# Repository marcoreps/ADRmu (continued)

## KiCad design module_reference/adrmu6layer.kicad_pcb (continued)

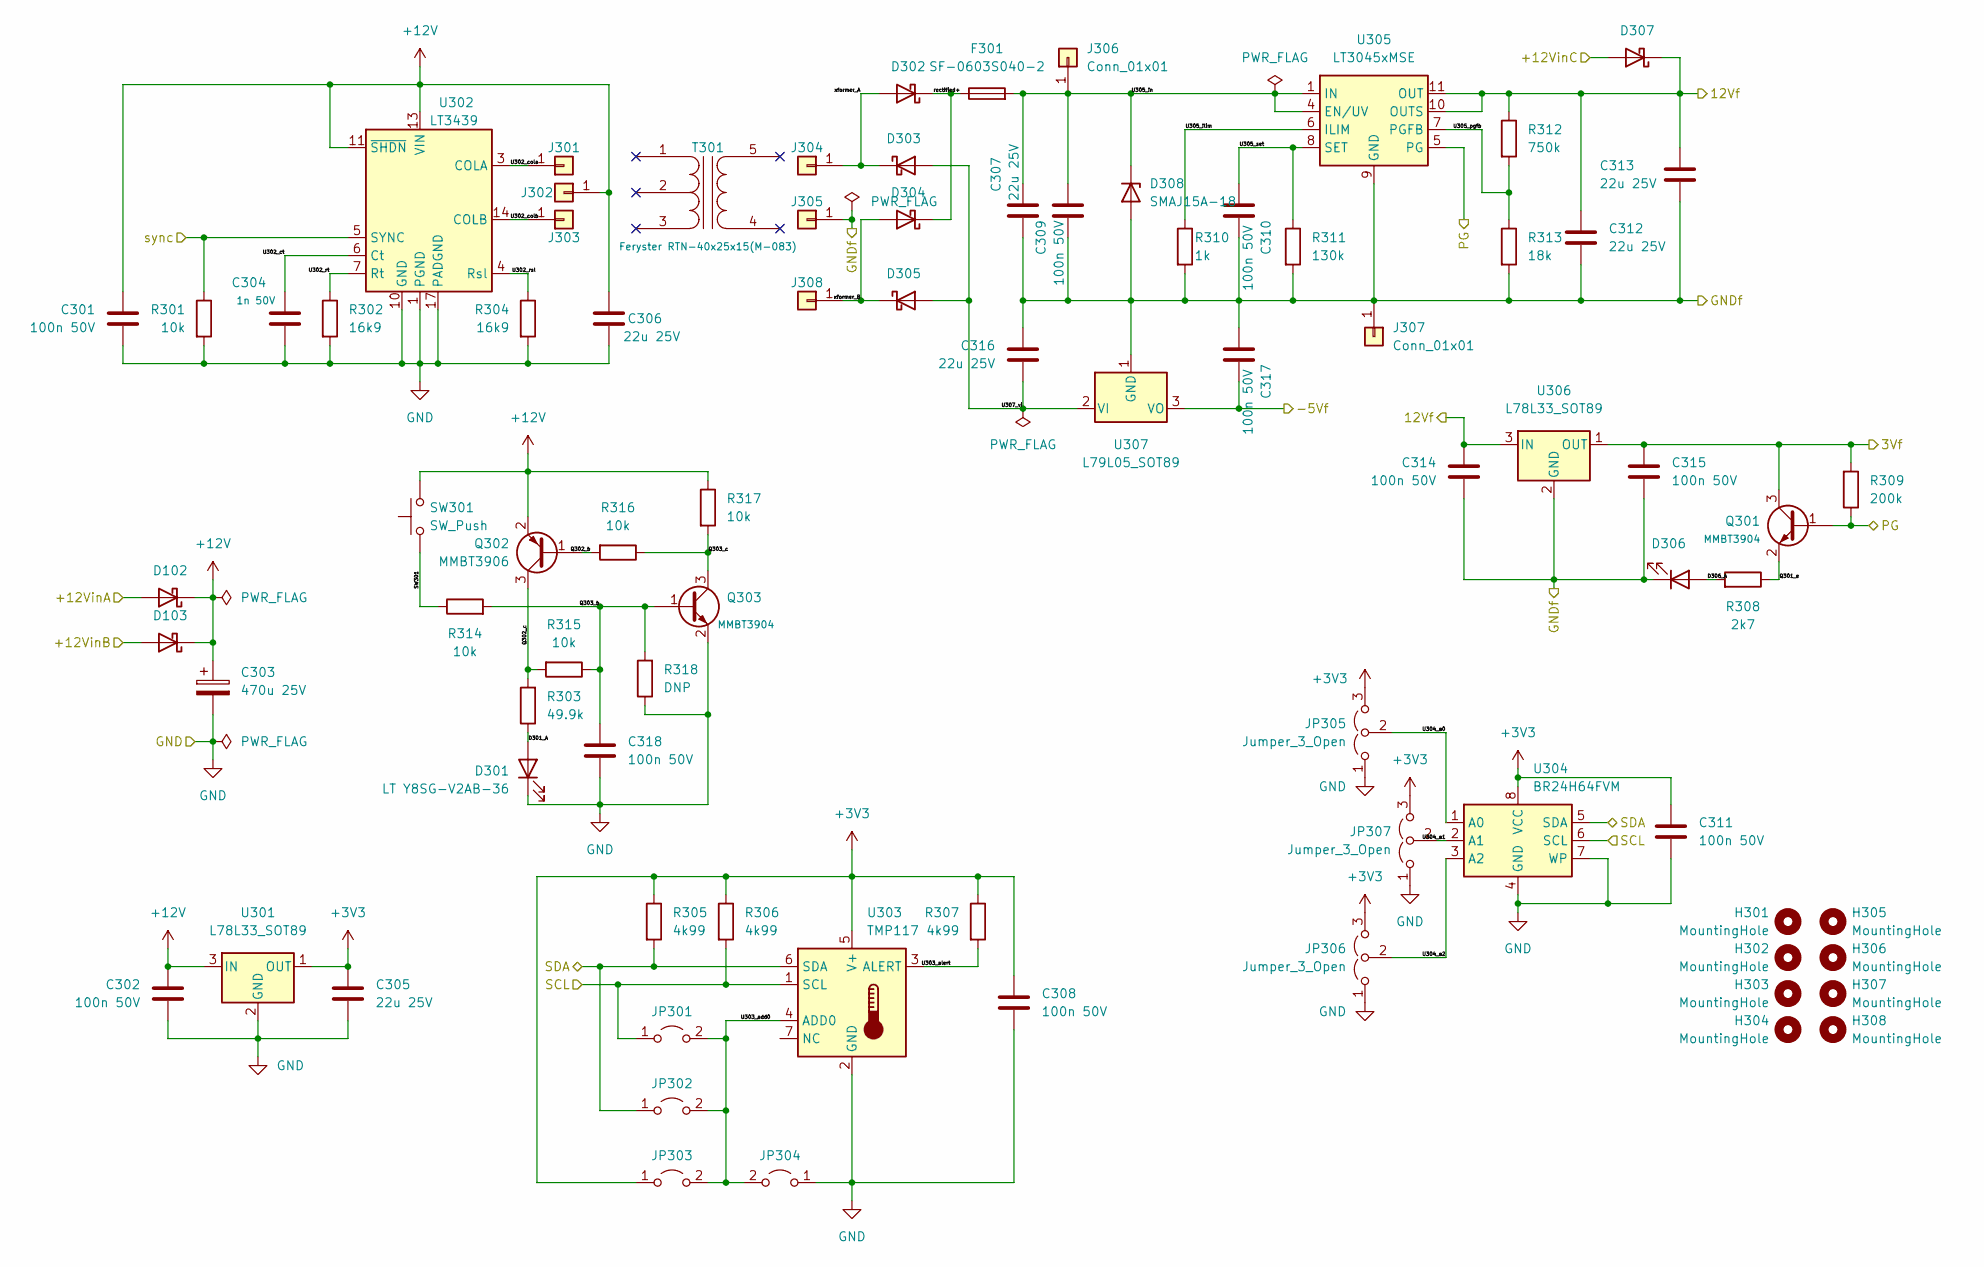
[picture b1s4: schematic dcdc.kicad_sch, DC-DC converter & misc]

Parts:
C301, C302, C308, C309, C310, C311, C314, C315, C317, C318: 100n 50V; C_0603_1608Metric
C303: 470u 25V; CP_Radial_D16.0mm_P7.50mm
C304: 1n 50V; C_0805_2012Metric
C305, C306, C307, C312, C313, C316: 22u 25V; C_1206_3216Metric
D102, D103, D302, D303, D304, D305, D307: PMEG6010CEH; D_SOD-123F
D301, D306: LT Y8SG-V2AB-36; LED_1206_3216Metric
D308: SMAJ15A-18; D_SMA
F301: SF-0603S040-2; Fuse_0603_1608Metric
H301, H302, H303, H304, H305, H306, H307, H308: MountingHole; MountingHole_4.3mm_M4
J301, J302, J303, J304, J305, J308: Conn_01x01; SolderWire-1sqmm_1x01_D1.4mm_OD3.9mm
J306, J307: Conn_01x01; SolderWirePad_1x01_SMD_1x2mm
JP301, JP302, JP303, JP304: Jumper_2_Open; SolderJumper-2_P1.3mm_Open_RoundedPad1.0x1.5mm
JP305, JP306, JP307: Jumper_3_Open; SolderJumper-3_P1.3mm_Open_RoundedPad1.0x1.5mm_NumberLabels
Q301, Q303: MMBT3904; SOT-23
Q302: MMBT3906; SOT-23
R301, R314, R315, R316, R317: 10k; R_0805_2012Metric
R302, R304: 16k9; R_0805_2012Metric
R303: 49.9k; R_0805_2012Metric
R305, R306, R307: 4k99; R_0805_2012Metric
R308: 2k7; R_0805_2012Metric
R309: 200k; R_0805_2012Metric
R310: 1k; R_0805_2012Metric
R311: 130k; R_0805_2012Metric
R312: 750k; R_0805_2012Metric
R313: 18k; R_0805_2012Metric
R318: DNP; R_0805_2012Metric
SW301: SW_Push; SW_Tactile_SPST_Angled_PTS645Vx31-2LFS
T301: Feryster RTN-40x25x15(M-083)
U301, U306: L78L33_SOT89; SOT-89-3
U302: LT3439; TSSOP-16-1EP_4.4x5mm_P0.65mm
U303: TMP117; WSON-6-1EP_2x2mm_P0.65mm_EP1x1.6mm
U304: BR24H64FVM; MSOP-8_3x3mm_P0.65mm
U305: LT3045xMSE; MSOP-12-1EP_3x4mm_P0.65mm_EP1.65x2.85mm
U307: L79L05_SOT89; SOT-89-3

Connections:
+3V3: C305.1, C308.1, C311.1, JP303.1 (A), JP305.3 (B), JP306.3 (B), JP307.3 (B), R305.1, R306.1, R307.1, U301.1 (OUT), U303.5 (V+), U304.8 (VCC)
+12V: C301.1, C302.1, C303.1, C306.1, D102.1 (K), D103.1 (K), J302.1, Q302.2 (E), R317.1, SW301.2, U301.3 (IN), U302.11 (~SHDN), U302.13 (VIN)
/Buffer/3Vf: C315.1, Q301.3 (C), R309.2, U306.1 (OUT); also elsewhere on the board
/Buffer/12Vf: C312.1, C313.1, C314.1, D307.1 (K), R312.1, U305.10 (OUTS), U305.11 (OUT), U305.12 (OUT), U306.3 (IN); also elsewhere on the board
/Buffer/-5Vf: C317.2, U307.3 (VO); also elsewhere on the board
/Buffer/FF: Q301.1 (B), R309.1, U305.5 (PG); also elsewhere on the board
/Buffer/GNDf: C307.2, C309.2, C310.2, C312.2, C313.2, C314.2, C315.2, C316.1, C317.1, D306.1 (K), D308.2 (A), J305.1, J307.1, R310.2, R311.2, R313.2, U305.9 (GND), U305.13 (GND), U306.2 (GND), U307.1 (GND); also elsewhere on the board
/DC-DC converter/+12VinA: D102.2 (A); also elsewhere on the board
/DC-DC converter/+12VinB: D103.2 (A); also elsewhere on the board
/DC-DC converter/+12VinC: D307.2 (A); also elsewhere on the board
/DC-DC converter/D301_A: D301.2 (A), R303.1
/DC-DC converter/D306_A: D306.2 (A), R308.2
/DC-DC converter/Q301_e: Q301.2 (E), R308.1
/DC-DC converter/Q302_b: Q302.1 (B), R316.2
/DC-DC converter/Q302_c: Q302.3 (C), R303.2, R315.2
/DC-DC converter/Q303_b: C318.1, Q303.1 (B), R314.2, R315.1, R318.2
/DC-DC converter/Q303_c: Q303.3 (C), R316.1, R317.2
/DC-DC converter/SCL: JP301.1 (A), R306.2, U303.1 (SCL), U304.6 (SCL); also elsewhere on the board
/DC-DC converter/SDA: JP302.1 (A), R305.2, U303.6 (SDA), U304.5 (SDA); also elsewhere on the board
/DC-DC converter/SW301: R314.1, SW301.1
/DC-DC converter/U302_cola: J301.1, U302.3 (COLA)
/DC-DC converter/U302_colb: J303.1, U302.14 (COLB)
/DC-DC converter/U302_ct: C304.1, U302.6 (Ct)
/DC-DC converter/U302_rsl: R304.1, U302.4 (Rsl)
/DC-DC converter/U302_rt: R302.1, U302.7 (Rt)
/DC-DC converter/U303_add0: JP301.2 (B), JP302.2 (B), JP303.2 (B), JP304.2 (B), U303.4 (ADD0)
/DC-DC converter/U303_alert: R307.2, U303.3 (ALERT)
/DC-DC converter/U304_a0: JP305.2 (C), U304.1 (A0)
/DC-DC converter/U304_a1: JP307.2 (C), U304.2 (A1)
/DC-DC converter/U304_a2: JP306.2 (C), U304.3 (A2)
/DC-DC converter/U305_ilim: R310.1, U305.6 (ILIM)
/DC-DC converter/U305_in: C307.1, C309.1, D308.1 (K), F301.2, J306.1, U305.1 (IN), U305.2 (IN), U305.3 (IN), U305.4 (EN/UV)
/DC-DC converter/U305_pgfb: R312.2, R313.1, U305.7 (PGFB)
/DC-DC converter/U305_set: C310.1, R311.1, U305.8 (SET)
/DC-DC converter/U307_vi: C316.2, D303.2 (A), D305.2 (A), U307.2 (VI)
/DC-DC converter/rectified+: D302.1 (K), D304.1 (K), F301.1
/DC-DC converter/sync: R301.1, U302.5 (SYNC); also elsewhere on the board
/DC-DC converter/xformer_A: D302.2 (A), D303.1 (K), J304.1
/DC-DC converter/xformer_B: D304.2 (A), D305.1 (K), J308.1
GND: C301.2, C302.2, C303.2, C304.2, C305.2, C306.2, C308.2, C311.2, C318.2, D301.1 (K), JP304.1 (A), JP305.1 (A), JP306.1 (A), JP307.1 (A), Q303.2 (E), R301.2, R302.2, R304.2, R318.1, U301.2 (GND), U302.1 (PGND), U302.10 (GND), U302.16 (PGND), U302.17 (PADGND), U303.2 (GND), U304.4 (GND), U304.7 (WP); also elsewhere on the board

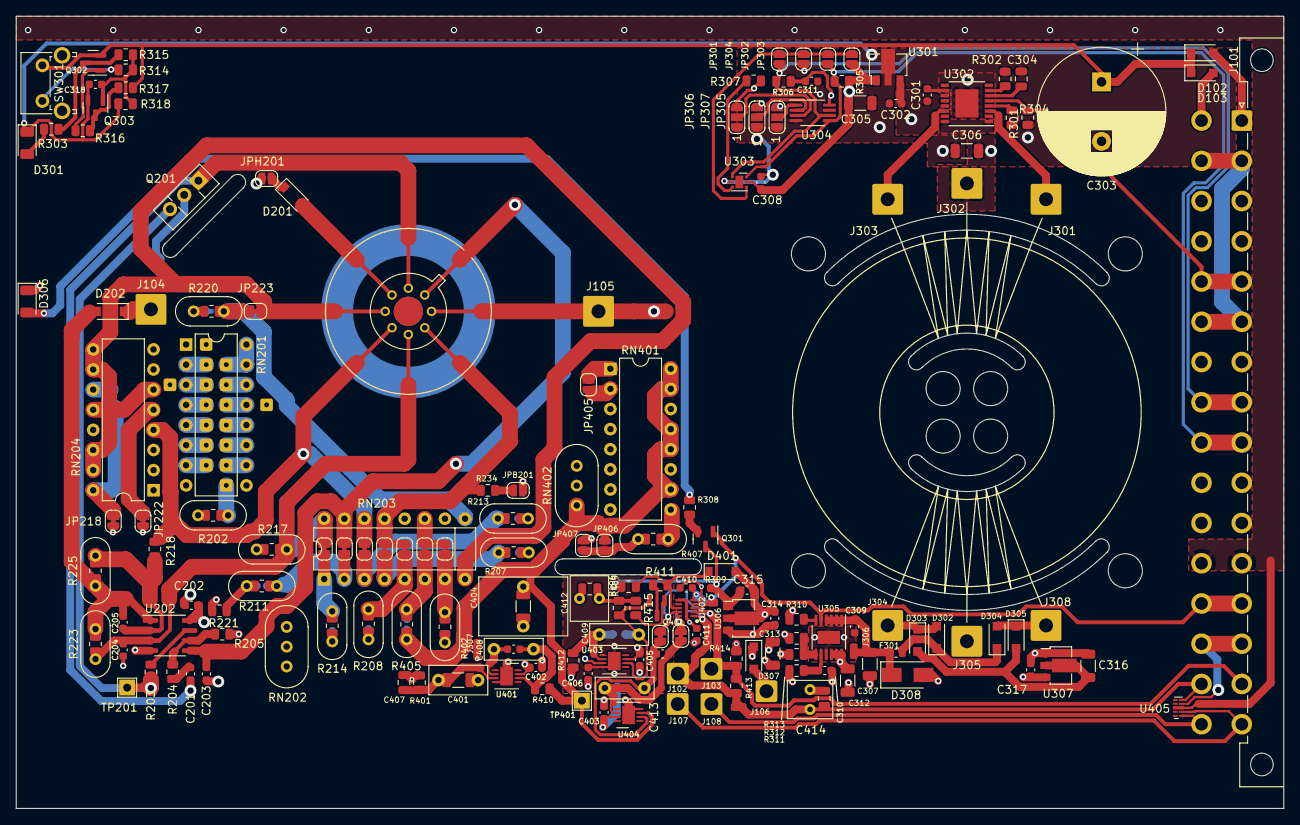
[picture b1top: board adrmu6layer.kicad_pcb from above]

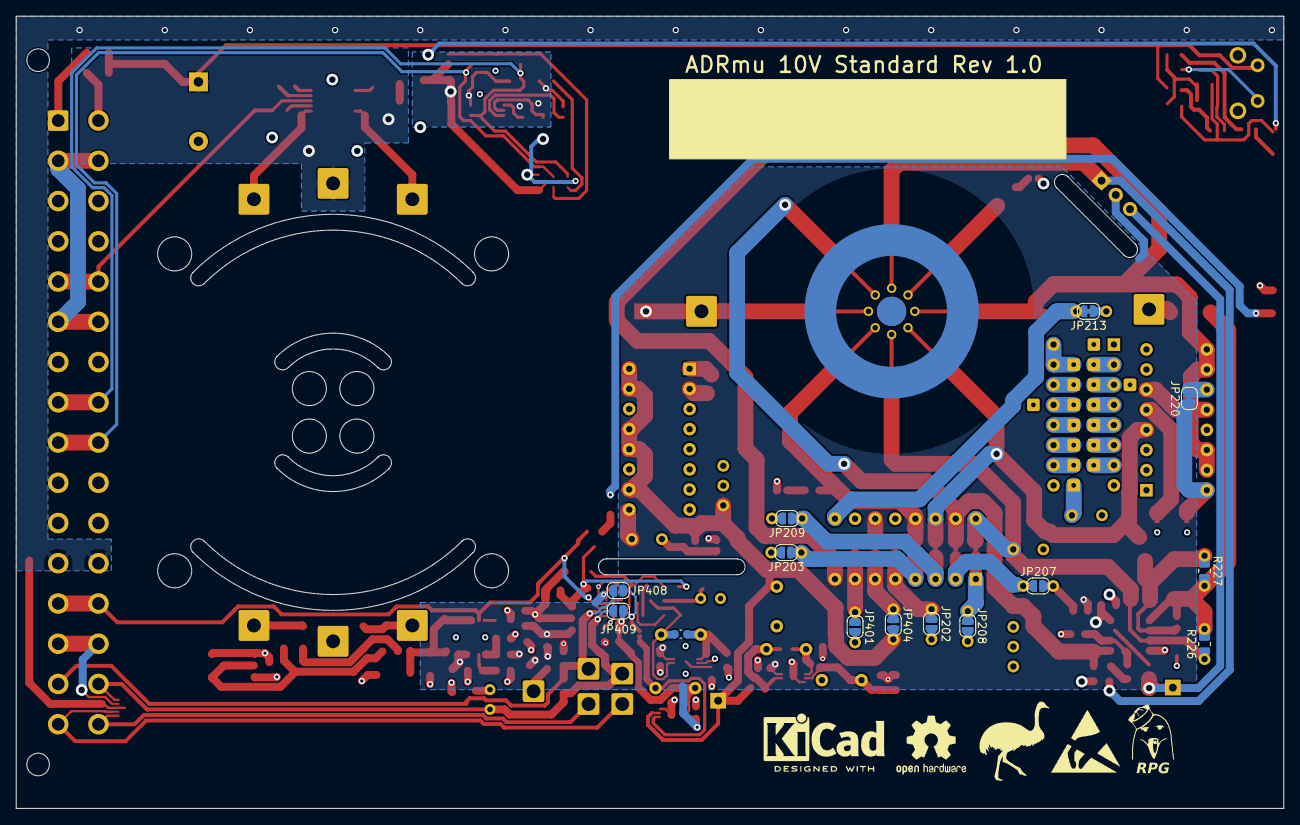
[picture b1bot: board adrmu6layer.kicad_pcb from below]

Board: 6 copper layers, 160.0 x 100.0 mm, 229 parts (19 on the bottom side), 101 nets.

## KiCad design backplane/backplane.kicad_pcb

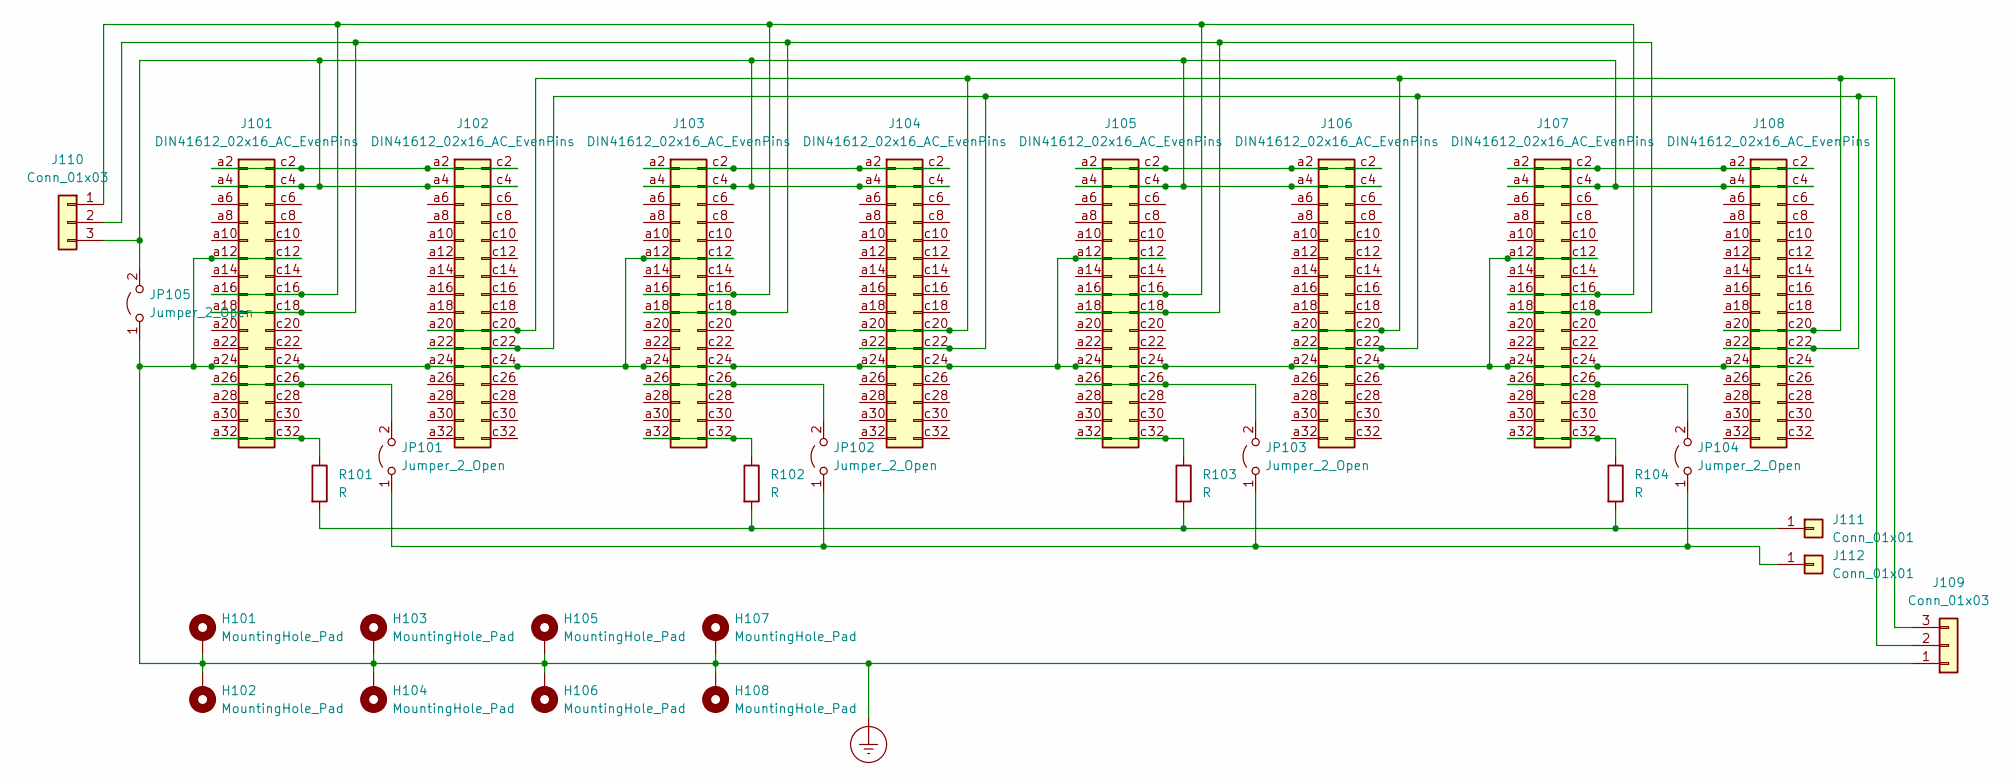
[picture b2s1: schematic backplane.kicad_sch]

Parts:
H101, H102, H103, H104, H105, H106, H107, H108: MountingHole_Pad; MountingHole_2.5mm_Pad
J101, J102, J103, J104, J105, J106, J107, J108: DIN41612_02x16_AC_EvenPins; DIN41612_C_2x16_Female_Vertical_THT
J109: Conn_01x03; TerminalBlock_WAGO_804-103_1x03_P5.00mm_45Degree
J110: Conn_01x03; JST_XH_B3B-XH-A_1x03_P2.50mm_Vertical
J111, J112: Conn_01x01; SolderWire-0.5sqmm_1x01_D0.9mm_OD2.1mm
JP101, JP102, JP103, JP104, JP105: Jumper_2_Open; SolderJumper-2_P1.3mm_Open_RoundedPad1.0x1.5mm
R101, R102, R103, R104: R; R_0805_2012Metric

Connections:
Earth_Protective: H101.1, H102.1, H103.1, H104.1, H105.1, H106.1, H107.1, H108.1, J101.a12, J101.a24, J101.c12, J101.c24, J102.a24, J102.c24, J103.a12, J103.a24, J103.c12, J103.c24, J104.a24, J104.c24, J105.a12, J105.a24, J105.c12, J105.c24, J106.a24, J106.c24, J107.a12, J107.a24, J107.c12, J107.c24, J108.a24, J108.c24, J109.1, JP105.1 (A)
unnamed: J101.a2, J101.c2, J102.a2, J102.c2
unnamed: J101.a16, J101.c16, J103.a16, J103.c16, J105.a16, J105.c16, J107.a16, J107.c16, J110.1
unnamed: J101.a18, J101.c18, J103.a18, J103.c18, J105.a18, J105.c18, J107.a18, J107.c18, J110.2
unnamed: J101.a26, J101.c26, JP101.2 (B)
unnamed: J101.a32, J101.c32, R101.1
unnamed: J102.a20, J102.c20, J104.a20, J104.c20, J106.a20, J106.c20, J108.a20, J108.c20, J109.3
unnamed: J102.a22, J102.c22, J104.a22, J104.c22, J106.a22, J106.c22, J108.a22, J108.c22, J109.2
unnamed: J103.a2, J103.c2, J104.a2, J104.c2
unnamed: J103.a26, J103.c26, JP102.2 (B)
unnamed: J103.a32, J103.c32, R102.1
unnamed: J105.a2, J105.c2, J106.a2, J106.c2
unnamed: J105.a26, J105.c26, JP103.2 (B)
unnamed: J105.a32, J105.c32, R103.1
unnamed: J107.a2, J107.c2, J108.a2, J108.c2
unnamed: J107.a26, J107.c26, JP104.2 (B)
unnamed: J107.a32, J107.c32, R104.1
unnamed: J101.a4, J101.c4, J102.a4, J102.c4, J103.a4, J103.c4, J104.a4, J104.c4, J105.a4, J105.c4, J106.a4, J106.c4, J107.a4, J107.c4, J108.a4, J108.c4, J110.3, JP105.2 (B)
unnamed: J111.1, R101.2, R102.2, R103.2, R104.2
unnamed: J112.1, JP101.1 (A), JP102.1 (A), JP103.1 (A), JP104.1 (A)

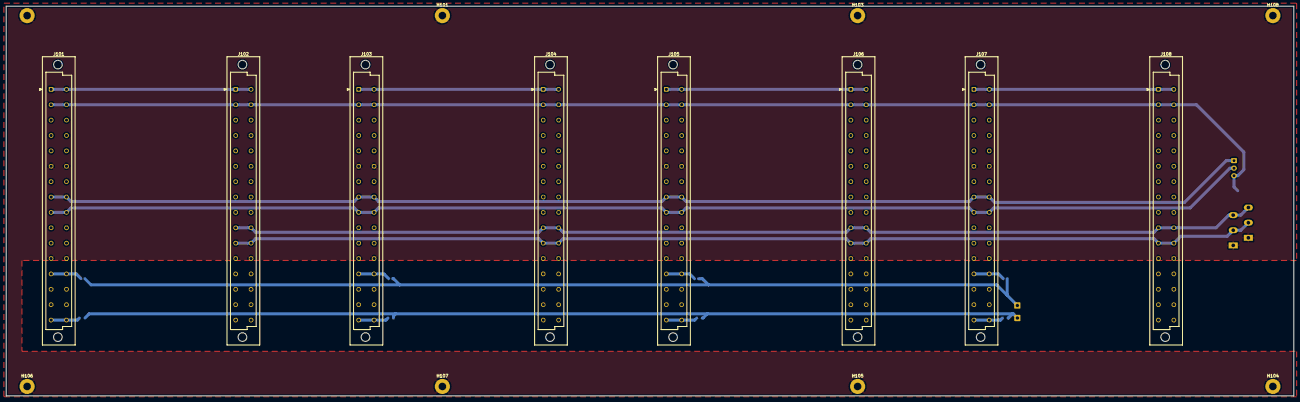
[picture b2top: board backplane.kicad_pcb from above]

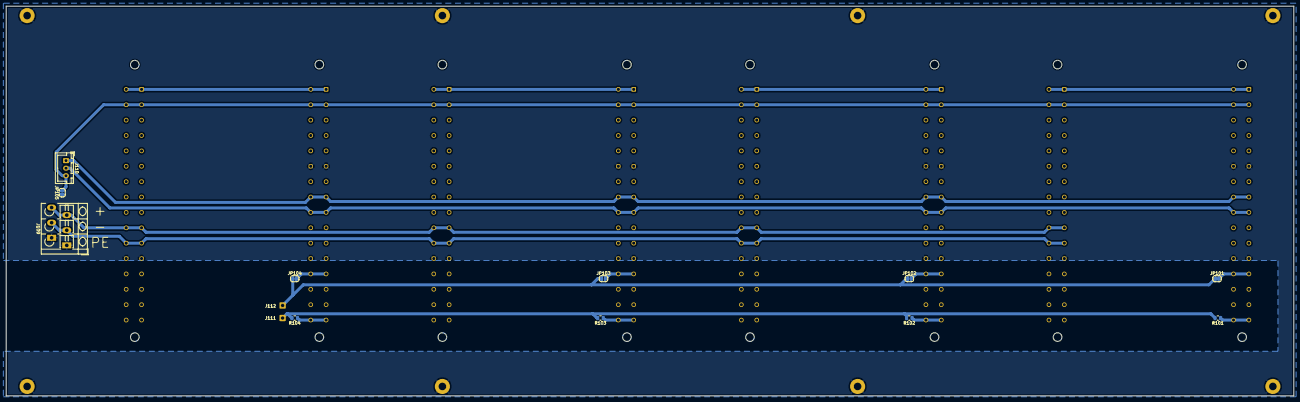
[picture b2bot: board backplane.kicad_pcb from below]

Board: 2 copper layers, 425.3 x 128.7 mm, 29 parts (13 on the bottom side), 20 nets.

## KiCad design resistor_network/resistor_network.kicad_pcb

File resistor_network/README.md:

## Scope

This is an adapter for up to 8 SMD resistors to fit into a DIP16 footprint. Using this board one could assemble an all-in-one LTZ/ADR configuration and buffering resistor network out of good quality SMD thin film resistors such as RN73. When using a thermally conductive PCB substrate such as Al, Cu, AlN or Al2O3 the resistors are thermally coupled which can be an advantage. When populating the crystal heater circuit and providing it with power, Vref and GND, it will thermally stabilize the resistor networks temperature at around 40°C.

## Result

I have performed only one superficial test with such a network so far and it didn't look as good as the monolithic 8xthin film array method.

## Image

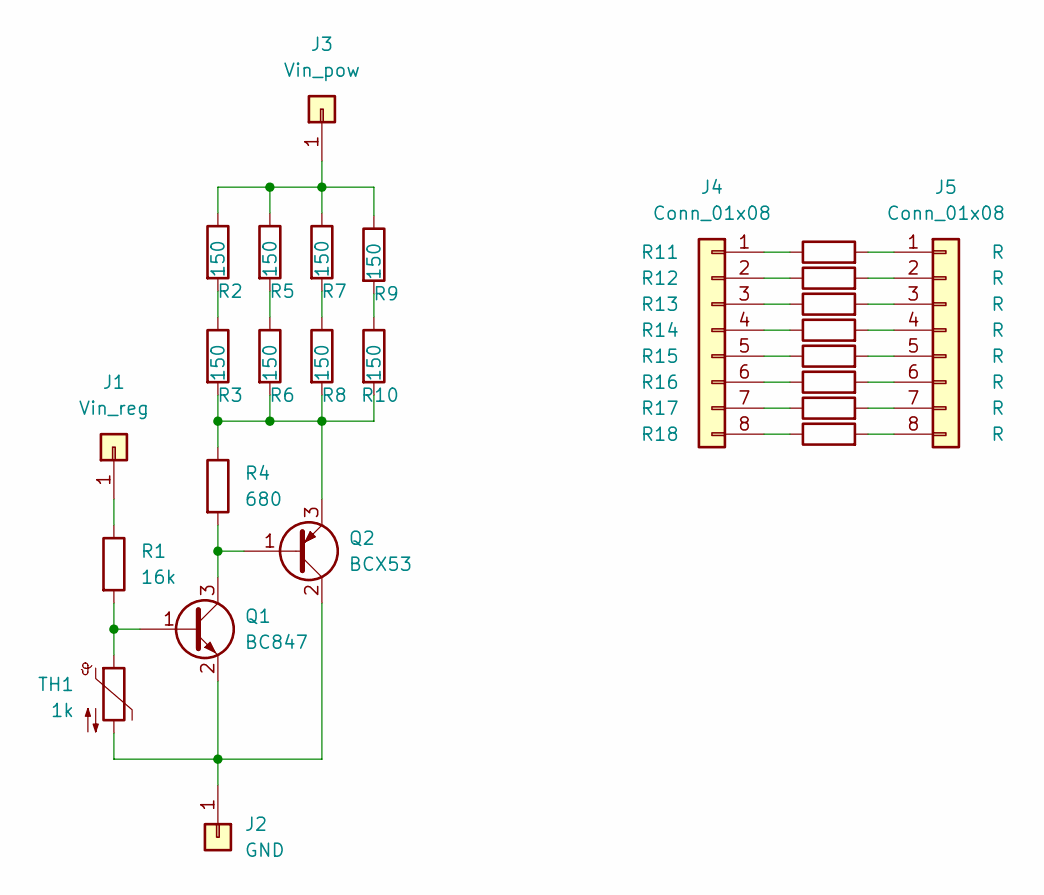
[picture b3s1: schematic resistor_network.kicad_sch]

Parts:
J1: Vin_reg; SolderWirePad_1x01_SMD_1x2mm
J2: GND; SolderWirePad_1x01_SMD_1x2mm
J3: Vin_pow; SolderWirePad_1x01_SMD_1x2mm
J4, J5: Conn_01x08; PinHeader_1x08_P2.54mm_Vertical_SMD_Pin1Left
Q1: BC847; SOT-23
Q2: BCX53; SOT-89-3
R1: 16k; R_0805_2012Metric
R2, R3, R5, R6, R7, R8, R9, R10: 150; R_1206_3216Metric
R4: 680; R_0805_2012Metric
R11, R12, R13, R14, R15, R16, R17, R18: R; R_1206_3216Metric
TH1: 1k; R_0805_2012Metric

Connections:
unnamed: J1.1, R1.1
unnamed: J2.1, Q1.2 (E), Q2.2 (C), TH1.2
unnamed: J3.1, R2.1, R5.1, R7.1, R9.1
unnamed: J4.1, R11.1
unnamed: J4.2, R12.1
unnamed: J4.3, R13.1
unnamed: J4.4, R14.1
unnamed: J4.5, R15.1
unnamed: J4.6, R16.1
unnamed: J4.7, R17.1
unnamed: J4.8, R18.1
unnamed: J5.1, R11.2
unnamed: J5.2, R12.2
unnamed: J5.3, R13.2
unnamed: J5.4, R14.2
unnamed: J5.5, R15.2
unnamed: J5.6, R16.2
unnamed: J5.7, R17.2
unnamed: J5.8, R18.2
unnamed: Q1.1 (B), R1.2, TH1.1
unnamed: Q1.3 (C), Q2.1 (B), R4.2
unnamed: Q2.3 (E), R3.2, R4.1, R6.2, R8.2, R10.2
unnamed: R2.2, R3.1
unnamed: R5.2, R6.1
unnamed: R7.2, R8.1
unnamed: R9.2, R10.1

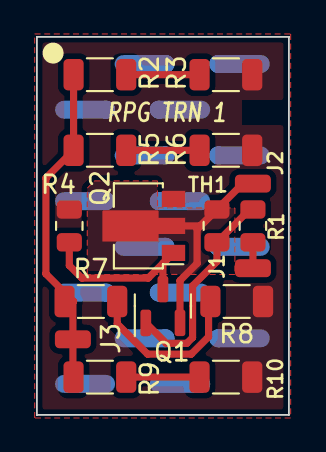
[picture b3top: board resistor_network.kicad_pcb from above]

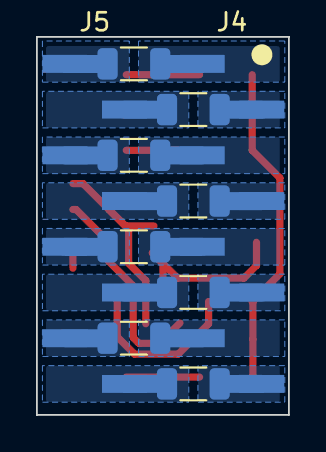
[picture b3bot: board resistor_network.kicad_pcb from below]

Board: 2 copper layers, 14.0 x 21.0 mm, 26 parts (10 on the bottom side), 26 nets.

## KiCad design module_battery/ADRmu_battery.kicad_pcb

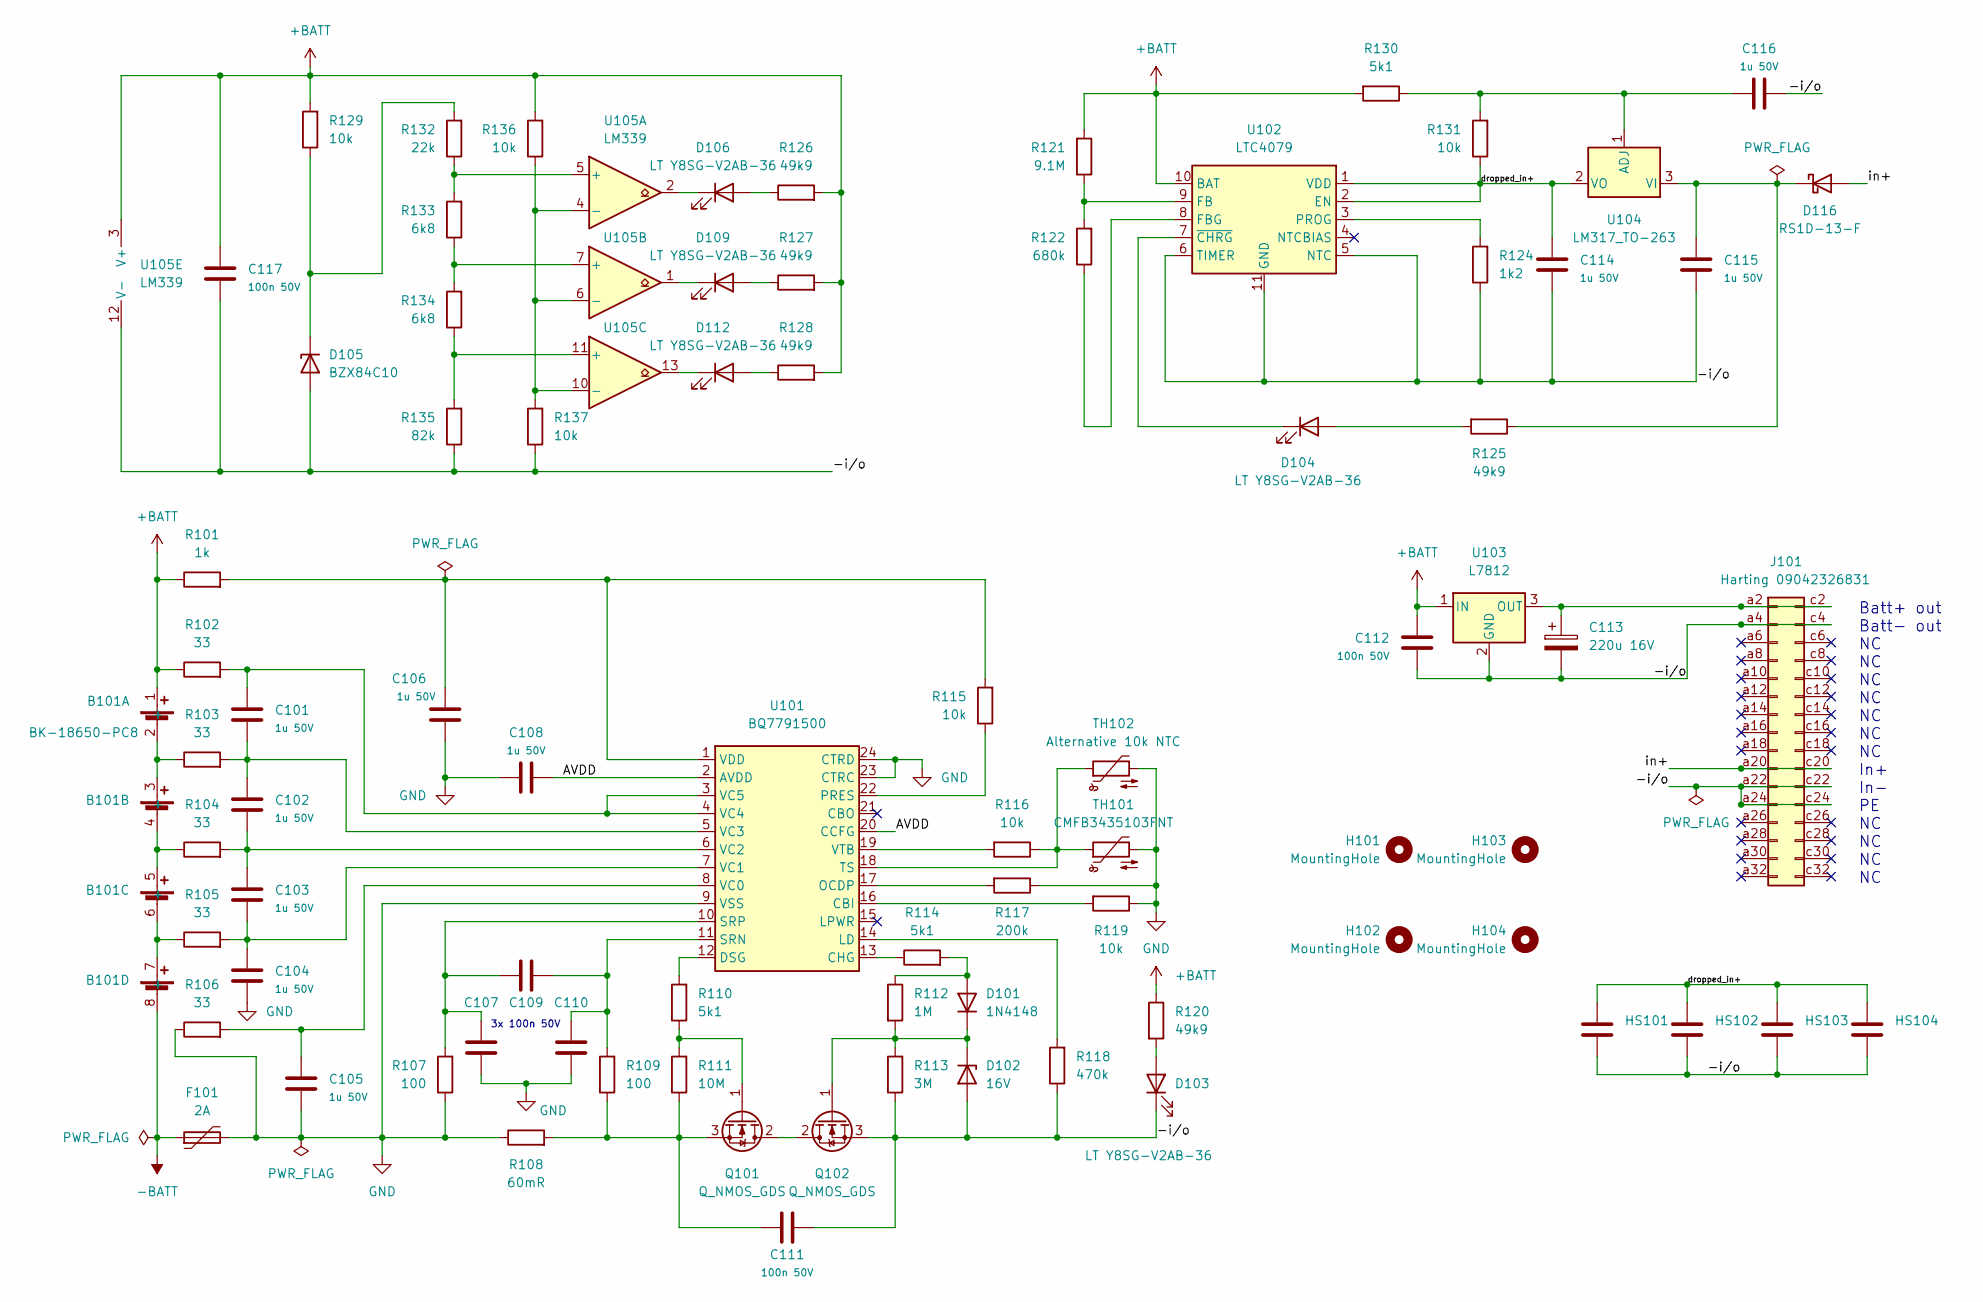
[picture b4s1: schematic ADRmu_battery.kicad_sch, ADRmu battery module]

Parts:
B101: BK-18650-PC8
C101, C102, C103, C104, C105, C106, C108, C114, C115, C116: 1u 50V; C_0805_2012Metric
C107, C109, C110, C111, C112, C117: 100n 50V; C_0805_2012Metric
C113: 220u 16V; CP_Radial_D10.0mm_P5.00mm
D101: 1N4148; D_SOD-123
D102: 16V; D_SOT-23_ANK
D103, D104, D106, D109, D112: LT Y8SG-V2AB-36; LED_1206_3216Metric
D105: BZX84C10; SOT-23
D116: RS1D-13-F; D_SMA
F101: 2A; Fuse_1812_4532Metric
H101, H102, H103, H104: MountingHole; MountingHole_5.3mm_M5
HS101, HS102, HS103, HS104: THJP1206AST1; C_1206_3216Metric
J101: Harting 09042326831; DIN41612_D_2x16_Male_Horizontal_THT
Q101, Q102: Q_NMOS_GDS; TO-252-2
R101: 1k; R_0805_2012Metric
R102, R103, R104, R105, R106: 33; R_0805_2012Metric
R107, R109: 100; R_0805_2012Metric
R108: 60mR; R_0805_2012Metric
R110, R114, R130: 5k1; R_0805_2012Metric
R111: 10M; R_0805_2012Metric
R112: 1M; R_0805_2012Metric
R113: 3M; R_0805_2012Metric
R115, R116, R119, R129, R131, R136, R137: 10k; R_0805_2012Metric
R117: 200k; R_0805_2012Metric
R118: 470k; R_0805_2012Metric
R120, R125, R126, R127, R128: 49k9; R_0805_2012Metric
R121: 9.1M; R_0805_2012Metric
R122: 680k; R_0805_2012Metric
R124: 1k2; R_0805_2012Metric
R132: 22k; R_0805_2012Metric
R133, R134: 6k8; R_0805_2012Metric
R135: 82k; R_0805_2012Metric
TH101: CMFB3435103FNT; R_0805_2012Metric
TH102: Alternative 10k NTC; R_Axial_DIN0204_L3.6mm_D1.6mm_P2.54mm_Vertical
U101: BQ7791500; TSSOP-24_4.4x7.8mm_P0.65mm
U102: LTC4079; DFN-10-1EP_3x3mm_P0.5mm_EP1.65x2.38mm
U103: L7812; TO-252-2
U104: LM317_TO-263; TO-263-2
U105: LM339; SOIC-14_3.9x8.7mm_P1.27mm

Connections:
+BATT: B101.1 (+), C112.2, C117.2, R101.1, R102.1, R120.1, R121.2, R126.2, R127.2, R128.2, R129.2, R130.2, R136.2, U102.10 (BAT), U103.1 (IN), U105.3 (V+)
-BATT: B101.8 (-), F101.1
/-i/o: C111.2, C112.1, C113.2, C114.2, C115.2, C116.2, C117.1, D102.2 (A), D103.1 (K), D105.1 (A), HS101.2, HS102.2, HS103.2, HS104.2, J101.a4, J101.a22, J101.a24, J101.c4, J101.c22, J101.c24, Q102.3 (S), R113.1, R118.1, R124.1, R135.1, R137.1, U102.5 (NTC), U102.6 (TIMER), U102.11 (GND), U103.2 (GND), U105.12 (V-)
/AVDD: C108.2, U101.2 (AVDD), U101.20 (CCFG)
/dropped_in+: C114.1, HS101.1, HS102.1, HS103.1, HS104.1, R131.1, U102.1 (VDD), U102.2 (EN), U104.2 (VO)
/in+: D116.2 (A), J101.a20, J101.c20
GND: C104.2, C105.2, C106.2, C107.1, C108.1, C110.1, F101.2, R106.1, R107.1, R108.1, R117.1, R119.1, TH101.2, TH102.2, U101.9 (VSS), U101.23 (CTRC), U101.24 (CTRD)
unnamed: B101.2 (-), B101.3 (+), R103.1
unnamed: B101.4 (-), B101.5 (+), R104.1
unnamed: B101.6 (-), B101.7 (+), R105.1
unnamed: C101.1, R102.2, U101.3 (VC5), U101.4 (VC4)
unnamed: C101.2, C102.1, R103.2, U101.5 (VC3)
unnamed: C102.2, C103.1, R104.2, U101.6 (VC2)
unnamed: C103.2, C104.1, R105.2, U101.7 (VC1)
unnamed: C105.1, R106.2, U101.8 (VC0)
unnamed: C106.1, R101.2, R115.2, U101.1 (VDD)
unnamed: C107.2, C109.1, R107.2, U101.10 (SRP)
unnamed: C109.2, C110.2, R109.2, U101.11 (SRN)
unnamed: C111.1, Q101.3 (S), R108.2, R109.1, R111.1
unnamed: C113.1, J101.a2, J101.c2, U103.3 (OUT)
unnamed: C115.1, D116.1 (K), R125.1, U104.3 (VI)
unnamed: C116.1, R130.1, R131.2, U104.1 (ADJ)
unnamed: D101.1 (K), D102.1 (K), Q102.1 (G), R112.2, R113.2
unnamed: D101.2 (A), R112.1, R114.2
unnamed: D103.2 (A), R120.2
unnamed: D104.1 (K), U102.7 (~CHRG)
unnamed: D104.2 (A), R125.2
unnamed: D105.3 (K), R129.1, R132.2
unnamed: D106.1 (K), U105.2
unnamed: D106.2 (A), R126.1
unnamed: D109.1 (K), U105.1
unnamed: D109.2 (A), R127.1
unnamed: D112.1 (K), U105.13
unnamed: D112.2 (A), R128.1
unnamed: Q101.1 (G), R110.1, R111.2
unnamed: Q101.2 (D), Q102.2 (D)
unnamed: R110.2, U101.12 (DSG)
unnamed: R114.1, U101.13 (CHG)
unnamed: R115.1, U101.22 (PRES)
unnamed: R116.1, TH101.1, TH102.1, U101.18 (TS)
unnamed: R116.2, U101.19 (VTB)
unnamed: R117.2, U101.17 (OCDP)
unnamed: R118.2, U101.14 (LD)
unnamed: R119.2, U101.16 (CBI)
unnamed: R121.1, R122.2, U102.9 (FB)
unnamed: R122.1, U102.8 (FBG)
unnamed: R124.2, U102.3 (PROG)
unnamed: R132.1, R133.2, U105.5 (+)
unnamed: R133.1, R134.2, U105.7 (+)
unnamed: R134.1, R135.2, U105.11 (+)
unnamed: R136.1, R137.2, U105.4 (-), U105.6 (-), U105.10 (-)

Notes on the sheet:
3x 100n 50V
Batt+ out Batt- out NC NC NC NC NC NC NC In+ In- PE NC NC NC NC

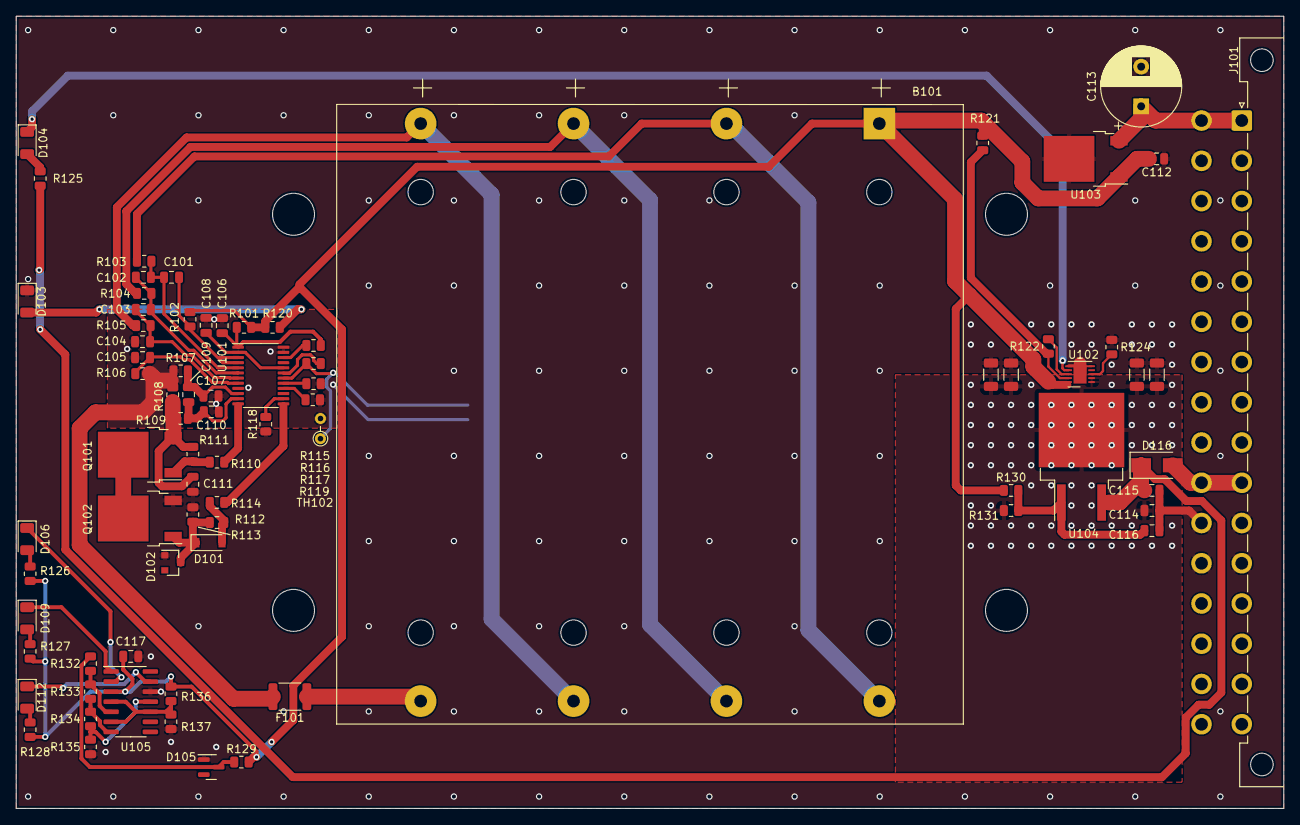
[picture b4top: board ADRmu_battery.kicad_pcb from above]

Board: 2 copper layers, 160.0 x 100.0 mm, 82 parts (1 on the bottom side), 51 nets.

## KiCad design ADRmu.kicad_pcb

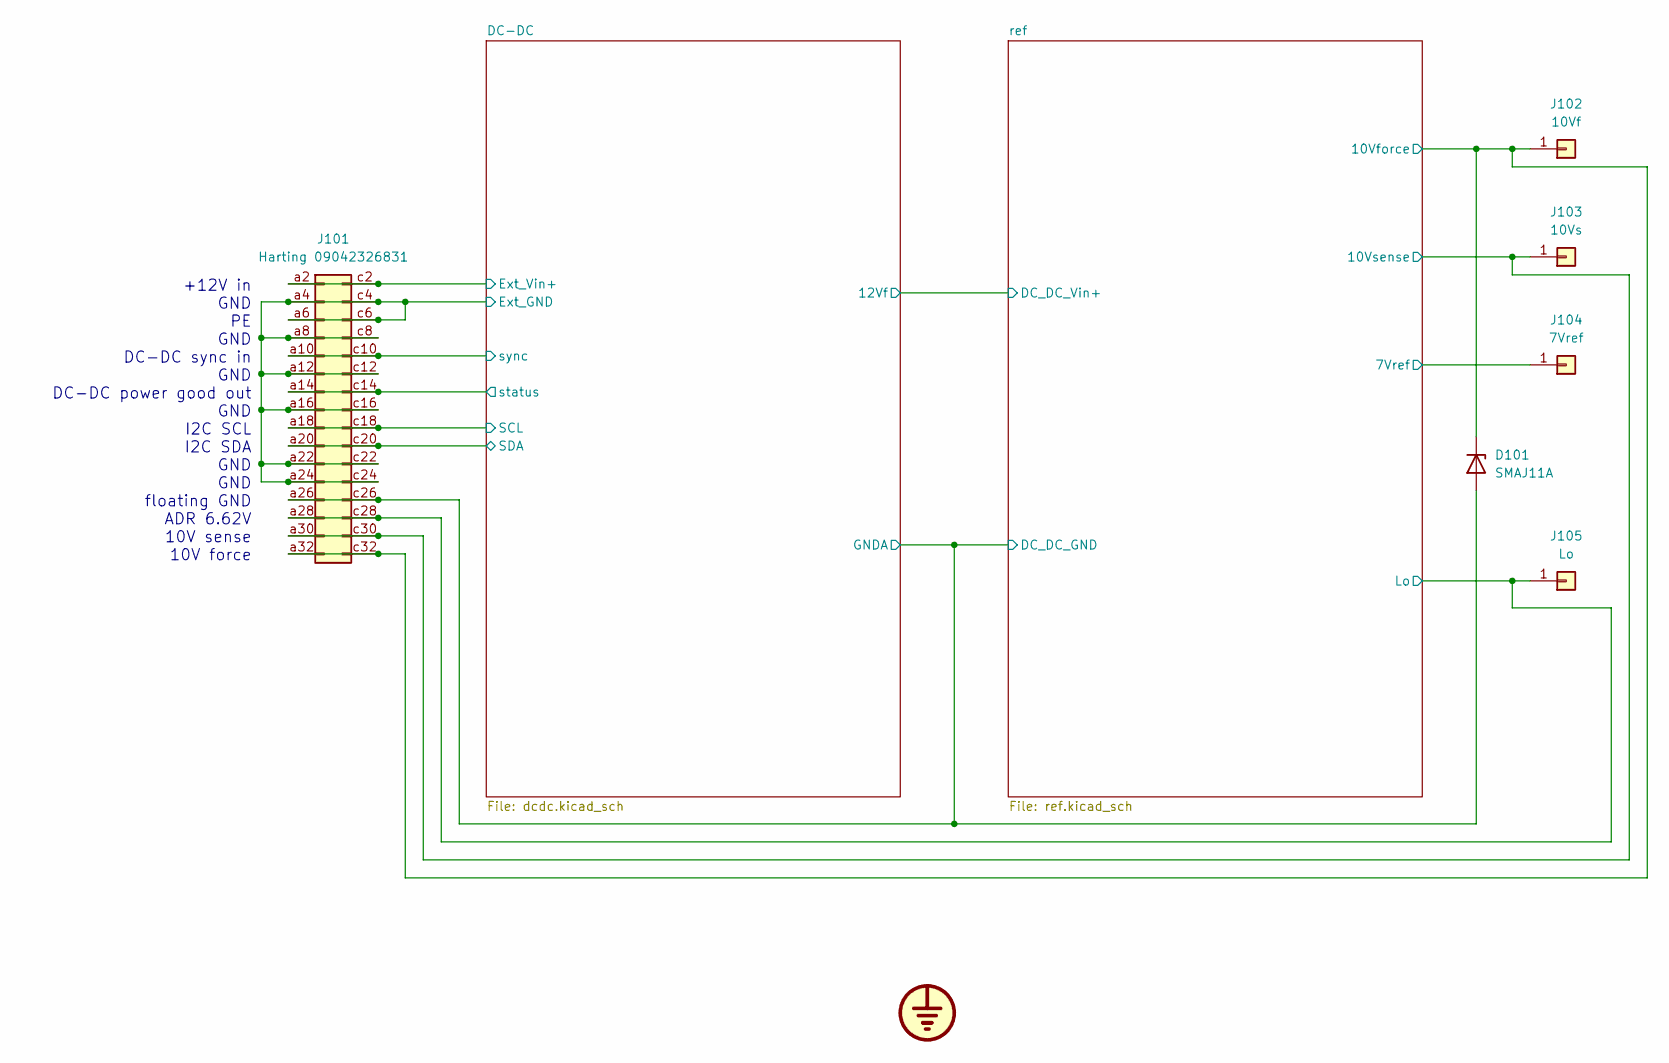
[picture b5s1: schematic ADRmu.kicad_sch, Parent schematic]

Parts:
D101: SMAJ11A‎; D_SMA
J101: Harting 09042326831; DIN41612_D_2x16_Male_Horizontal_THT
J102: 10Vf; SolderWire-1sqmm_1x01_D1.4mm_OD3.9mm
J103: 10Vs; SolderWire-1sqmm_1x01_D1.4mm_OD3.9mm
J104: 7Vref; SolderWire-1sqmm_1x01_D1.4mm_OD3.9mm
J105: Lo; SolderWire-1sqmm_1x01_D1.4mm_OD3.9mm
SYM101: OSMU; osmu_logo

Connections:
+12V: J101.a2, J101.c2; also elsewhere on the board
/DC-DC/SCL: J101.a18, J101.c18; also elsewhere on the board
/DC-DC/SDA: J101.a20, J101.c20; also elsewhere on the board
/DC-DC/status: J101.a14, J101.c14; also elsewhere on the board
/DC-DC/sync: J101.a10, J101.c10; also elsewhere on the board
/ref/7Vref: J104.1; also elsewhere on the board
/ref/10Vforce: D101.1 (K), J101.a32, J101.c32, J102.1; also elsewhere on the board
/ref/10Vsense: J101.a30, J101.c30, J103.1; also elsewhere on the board
/ref/ADR_Pin7: J101.a28, J101.c28, J105.1; also elsewhere on the board
GND: J101.a4, J101.a6, J101.a8, J101.a12, J101.a16, J101.a22, J101.a24, J101.c4, J101.c6, J101.c8, J101.c12, J101.c16, J101.c22, J101.c24; also elsewhere on the board
GNDA: D101.2 (A), J101.a26, J101.c26; also elsewhere on the board

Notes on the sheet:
+12V in GND PE GND DC-DC sync in GND DC-DC power good out GND I2C SCL I2C SDA GND GND floating GND ADR 6.62V 10V sense 10V force
